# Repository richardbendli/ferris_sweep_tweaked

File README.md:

# Tweaked Ferris Sweep

A fork of [David Barr's Sweep](https://github.com/davidphilipbarr/Sweep).

| Front | Back |
| :---: | :---: |
|  |  |
|  |  |
|  |  |

### Features

* Low profile Kailh Choc switches
* Hotswap
* Dual side-scrolling encoder
* Oled screens
* Power switch for battery management
* Bluetooth support w/ nice!nano
* Plate style case with mcu cover

### Components list

To build and use this Ferris Sweep you will need:

* 1 × PCB Kit (1.6mm thickness is good)
* 1 × back plate kit (optional, you can go for 1.2mm thickness)
* 2 × promicro compatible boards ( I used the Elite C ) or 2 x nice!nanos.
* 34 × Kailh Choc v1 switches
* 34 × Kailh Choc hotswap sockets (PG1350)
* 34 × keycaps
* 2 × side-scrolling encoders EVQWGD001
* 2 × OLED LCD Display 128x32 SSD1306 (optional)
* 2 × reset switches (optional; B3U-1000P(M))
* Some little rubber feet/bumpers (a minimum of 4 on each side)
* 2 × power switches (wireless only; MSK 12C02)
* 2 × lipo batteries (wireless only; 301230 or 301228)
* 1 × TRRS (not TRS!) cable (wired only)
* 2 × TRRS Jack [PJ-320A] (wired only)
* 1 × USB Cable (depends on your micro-controller choice)

##

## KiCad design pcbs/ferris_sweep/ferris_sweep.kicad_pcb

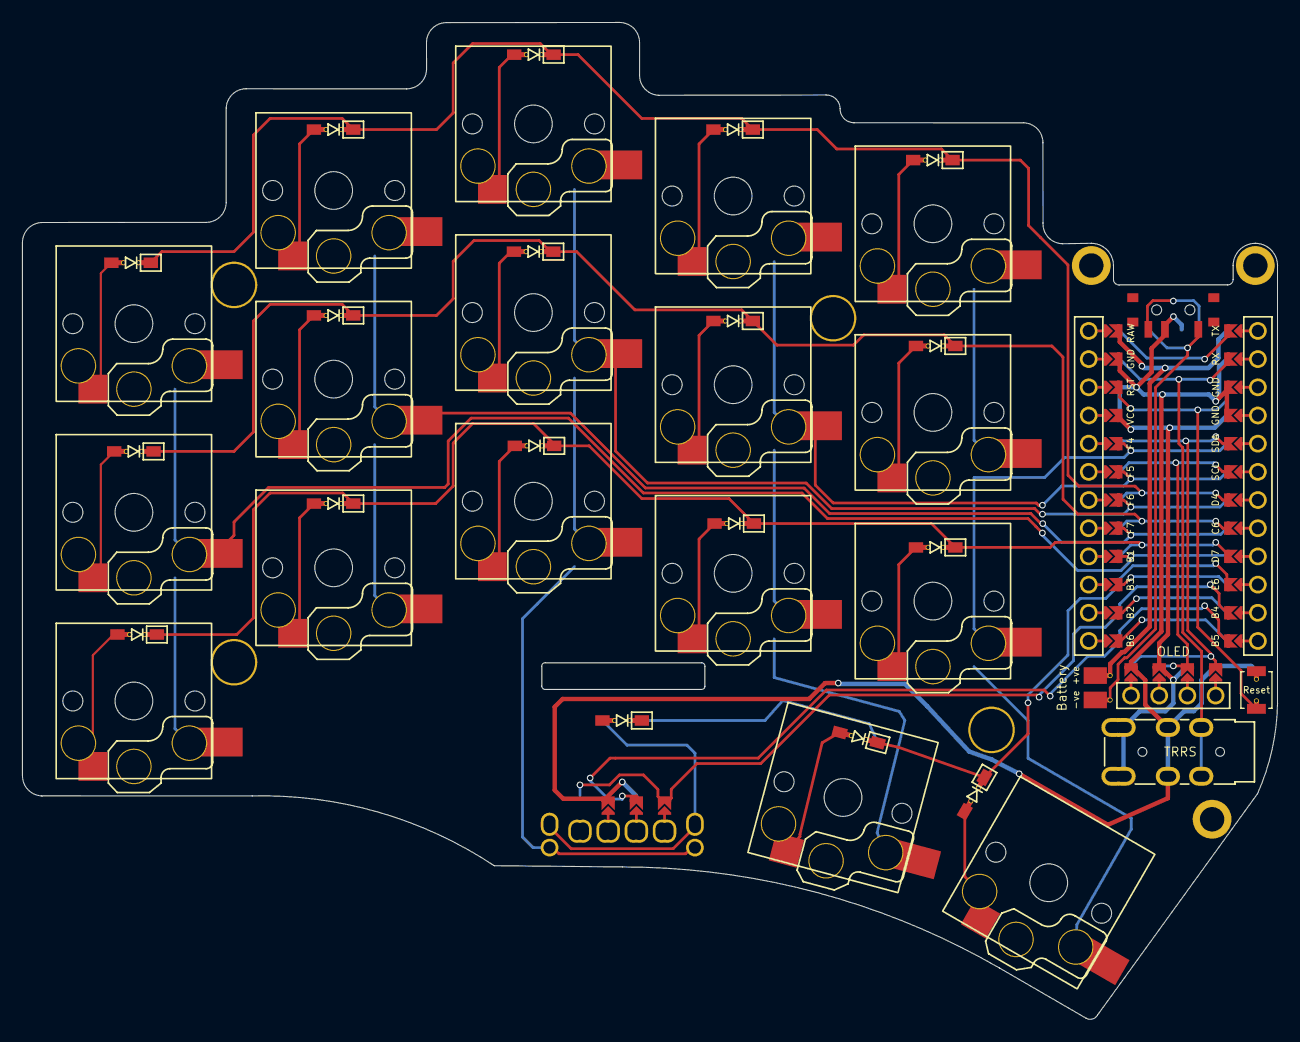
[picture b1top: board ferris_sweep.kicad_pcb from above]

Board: 2 copper layers, 113.1 x 89.8 mm, 49 parts (0 on the bottom side), 22 nets.

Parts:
BT1: Battery; Battery_pads_reversible
D1, D2, D3, D4, D5, D6, D7, D8, D9, D10, D11, D12, D13, D14, D15, D16, D17: 1N4148W; D3_SMD
ED1: 1N4148W; D3_SMD
EN2: EVQWGD001; RollerEncoder
H1, H2, H3, H4: M2 Hole; M2_hole_4.2mm
J1: TRRS; TRRS-3pin
O1: OLED; OLED_jumpers
PSW1: Power
RSW1: Reset
Ref**: Val**; M2_hole_3.5mm
Ref**#2, Ref**#3: Val**; M2_hole_3.5mm
SW1, SW2, SW3, SW4, SW5, SW6, SW7, SW8, SW9, SW10, SW11, SW12, SW13, SW14, SW15, SW16, SW17: Choc; Kailh-pg1350-socket-reversible
U1: ProMicro; ProMicro_jumpers

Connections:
GND: EN2.C, J1.C, O1.4, PSW1.2 (B), RSW1.2, U1.3 (GND), U1.4 (GND), U1.23 (GND)
unnamed: D1.2 (A), SW1.2
unnamed: D6.2 (A), SW6.2
unnamed: D11.2 (A), SW11.2
VCC: J1.A, J1.D, O1.3, U1.21 (VCC)
col0: SW1.1, SW6.1, SW11.1, U1.16 (B1)
col1: SW2.1, SW7.1, SW12.1, U1.17 (F7)
col2: EN2.S1, SW3.1, SW8.1, SW13.1, U1.18 (F6)
col3: SW4.1, SW9.1, SW14.1, SW16.1, U1.19 (F5)
col4: SW5.1, SW10.1, SW15.1, SW17.1, U1.20 (F4)
data: J1.B, U1.2 (RX)
eda: EN2.A, U1.11 (B4)
edb: EN2.B, U1.12 (B5)
er0: ED1.2 (A), EN2.S2
raw: BT1.1 (+), U1.24 (RAW)
reset: RSW1.1, U1.22 (RST)
row0: D1.1 (K), D2.1 (K), D3.1 (K), D4.1 (K), D5.1 (K), U1.7 (D4)
row1: D6.1 (K), D7.1 (K), D8.1 (K), D9.1 (K), D10.1 (K), U1.8 (C6)
row2: D11.1 (K), D12.1 (K), D13.1 (K), D14.1 (K), D15.1 (K), U1.9 (D7)
row3: D16.1 (K), D17.1 (K), ED1.1 (K), U1.10 (E6)
sda: O1.1, U1.5 (SDA)
sla: O1.2, U1.6 (SCL)

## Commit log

2023-08-28 Ferris Sweep
